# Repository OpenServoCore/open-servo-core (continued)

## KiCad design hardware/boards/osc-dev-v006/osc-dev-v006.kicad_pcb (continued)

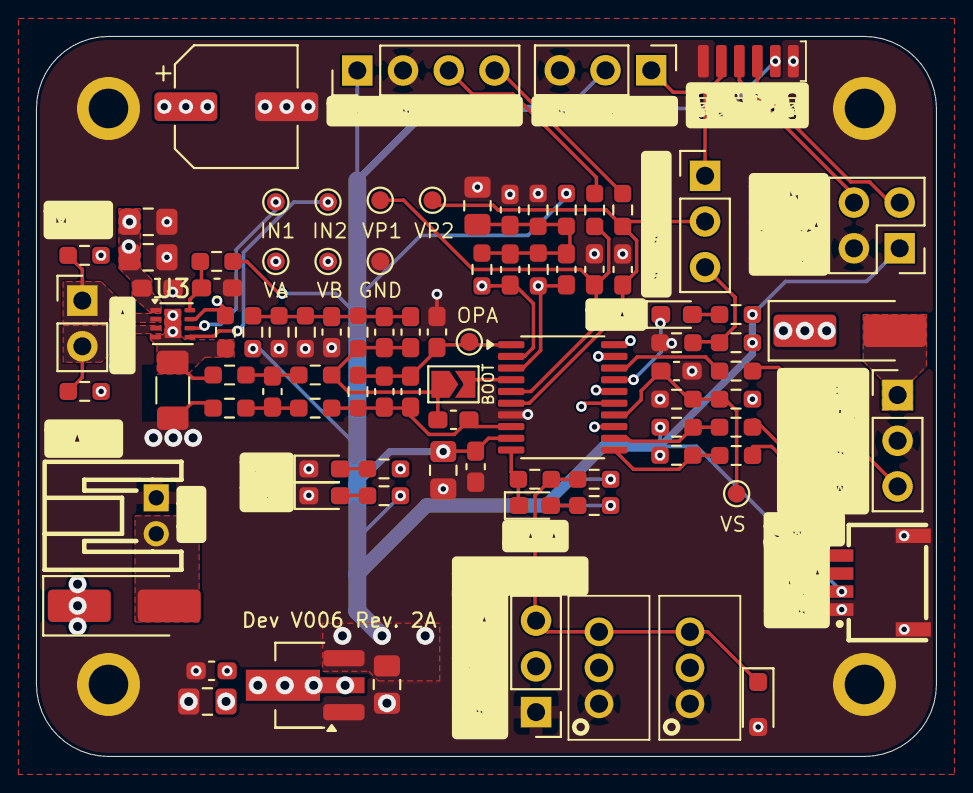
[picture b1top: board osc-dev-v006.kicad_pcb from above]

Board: 6 copper layers, 50.0 x 40.0 mm, 99 parts (0 on the bottom side), 46 nets.

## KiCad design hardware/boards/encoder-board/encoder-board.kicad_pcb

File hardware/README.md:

# KiCad Component Management

## Component Linkage System

### Directory Structure

```
hardware/
├── shared.kicad_sym        # Symbol library
├── shared.pretty/           # Footprint library
├── shared.3dshapes/         # 3D models
├── templates/jlc4l_1v6mm/   # Template project (canonical reference)
└── boards/*/                # Board projects
```

### Linkage Patterns

#### 1. Project → Libraries

Projects link to shared libraries via `sym-lib-table` and `fp-lib-table`:

- Symbol library: `${KIPRJMOD}/../../shared.kicad_sym`
- Footprint library: `${KIPRJMOD}/../../shared.pretty`

#### 2. Symbol → Footprint

Symbols in `shared.kicad_sym` reference footprints using library prefix:

- Format: `"shared:FOOTPRINT_NAME"`
- Example: `"shared:UQFN-20_L3.0-W3.0-P0.40-BL-EP1.7"`

#### 3. Footprint → 3D Model

Footprints in `shared.pretty/` reference 3D models using relative paths:

- Format: `${KIPRJMOD}/../../shared.3dshapes/MODEL_NAME.wrl`
- Example: `${KIPRJMOD}/../../shared.3dshapes/UQFN-20_L3.0-W3.0-P0.40-BL-EP1.7.wrl`

## Component Acquisition Strategy

1. Navigate to a board or template directory:

   ```bash
   cd hardware/templates/jlc4l_1v6mm
   ```

2. Download component:

   ```bash
   easyeda2kicad --full --lcsc_id <LCSC_ID> --output ../../shared --overwrite --project-relative
   ```

3. Fix 3D model paths in footprint files:
   - Find: `${KIPRJMOD}././shared.3dshapes`
   - Replace: `${KIPRJMOD}/../../shared.3dshapes`

4. In `shared.kicad_sym`, rename the `LCSC Part` property to `LCSC` on the downloaded symbol.

## Post-Import Checklist

- [ ] Symbol has correct footprint reference (`"shared:FOOTPRINT_NAME"`)
- [ ] Footprint has correct 3D model path (`${KIPRJMOD}/../../shared.3dshapes/...`)
- [ ] Pin types are correctly set: power_in (VCC/GND), input (control/data in), output (data out), passive (connectors) - NO "unspecified" pins allowed
- [ ] 3D model displays correctly in KiCad 3D viewer
- [ ] Symbol uses `LCSC` property (not `LCSC Part`) for the part number
- [ ] Component source documented (LCSC part number)

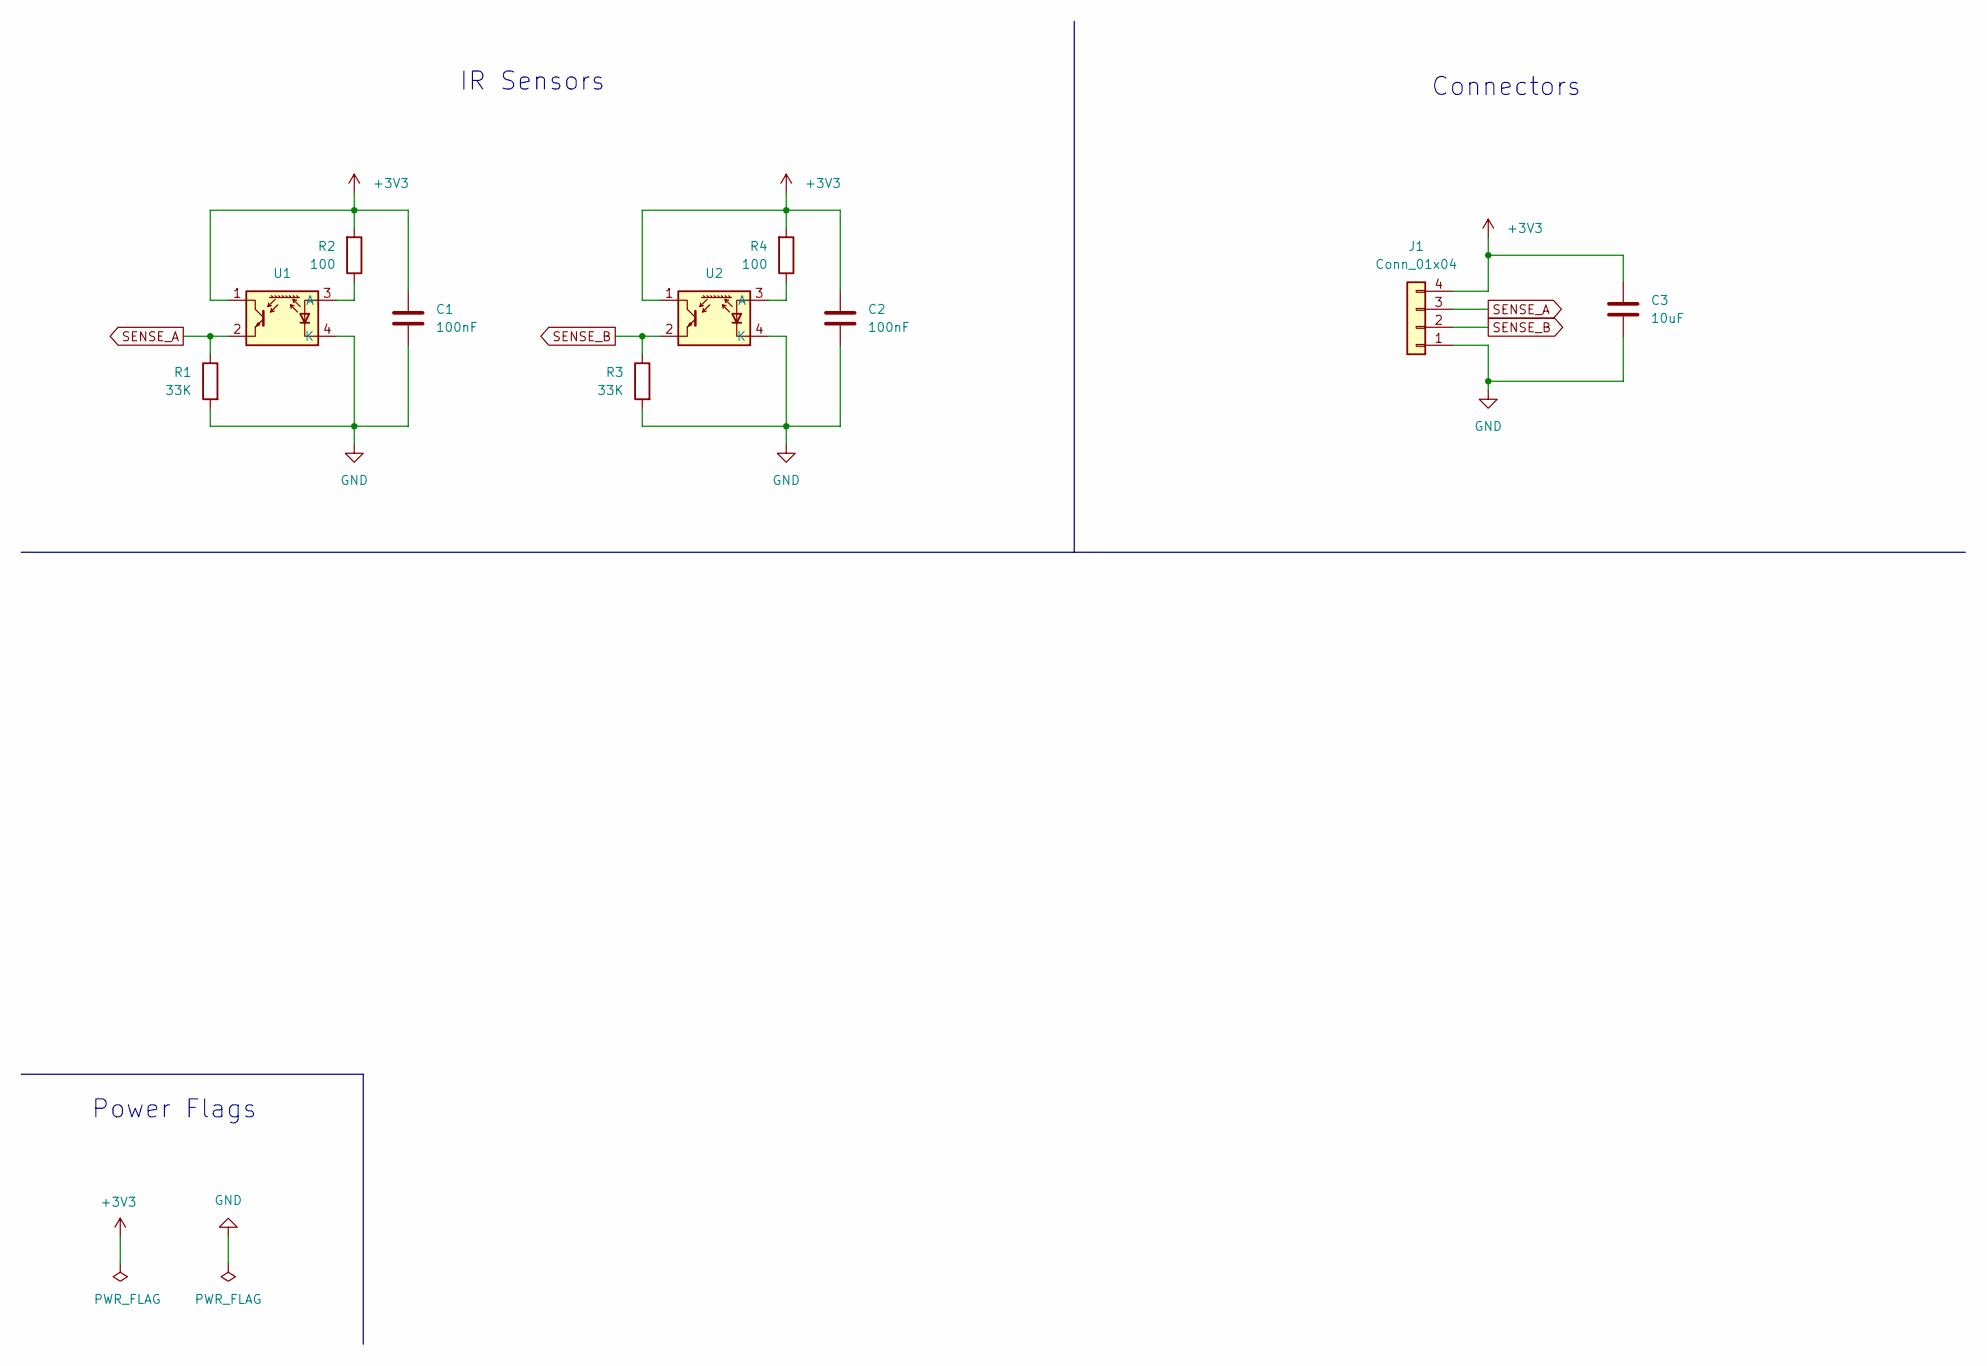
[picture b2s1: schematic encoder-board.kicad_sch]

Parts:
C1, C2: 100nF; C_0805_2012Metric_Pad1.18x1.45mm_HandSolder; LCSC C49678
C3: 10uF; C_0805_2012Metric_Pad1.18x1.45mm_HandSolder; LCSC C15850
J1: Conn_01x04; PinHeader_1x04_P2.54mm_Vertical; LCSC C780062
R1, R3: 33K; R_0805_2012Metric_Pad1.20x1.40mm_HandSolder; LCSC C17633
R2, R4: 100; R_0805_2012Metric_Pad1.20x1.40mm_HandSolder; LCSC C17408
U1, U2: ITR1204SR10A_TR(BY); OPTO-SMD-4_ITR1204SR10A; LCSC C475373

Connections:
+3V3: C1.1, C2.1, C3.1, J1.4, R2.2, R4.2, U1.1, U2.1
GND: C1.2, C2.2, C3.2, J1.1, R1.2, R3.2, U1.4 (K), U2.4 (K)
unnamed: R2.1, U1.3 (A)
unnamed: R4.1, U2.3 (A)
SENSE_A: J1.3, R1.1, U1.2
SENSE_B: J1.2, R3.1, U2.2

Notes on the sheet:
IR Sensors
Connectors
Power Flags

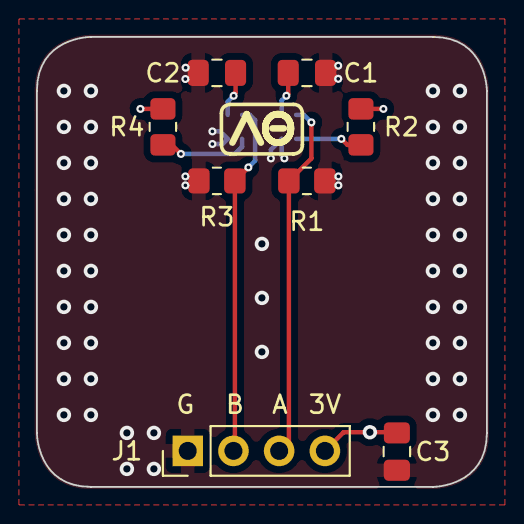
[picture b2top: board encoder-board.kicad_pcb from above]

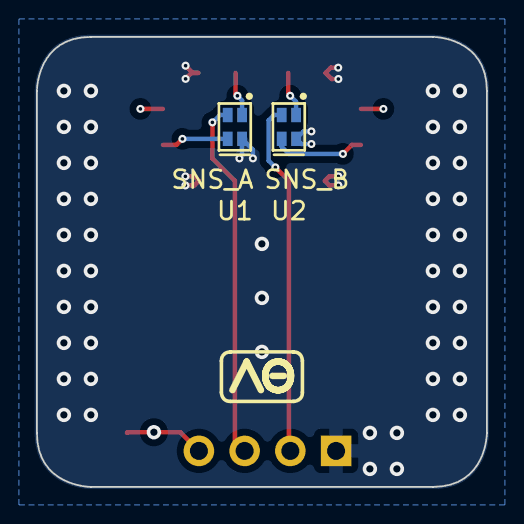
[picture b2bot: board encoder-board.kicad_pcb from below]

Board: 4 copper layers, 25.0 x 25.0 mm, 10 parts (2 on the bottom side), 6 nets.

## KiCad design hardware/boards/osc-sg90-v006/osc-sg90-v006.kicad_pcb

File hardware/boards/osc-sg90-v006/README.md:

# OSC SG90 CH32

> ⚠️ **Designed, not spun. Pre-fabrication, pre-bringup.**
> This board has never been fabbed. Numbers and behaviour described below are **design intent**, not measured. The schematic and layout exist; firmware v2 now runs on the dev board (the bus transport is silicon-proven) but has never run on *this* board. Don't fab this without doing your own review first, and expect changes when bringup finally happens.

OpenServoCore swap board for SG90-class hobby servos. Compact, double-sided, designed to physically replace the factory PCB inside an SG90 case. CH32V006-based, single-wire TTL servo bus (osc-native protocol), drop-in mechanical fit.

## Overview

- **MCU** — CH32V006F8U6 (RISC-V, 48 MHz, 62 KB flash, 8 KB RAM).
- **Motor driver** — TI DRV8837 H-bridge (1.8 A peak, IN1/IN2 PWM).
- **LDO** — TPAP2210K-3.3, 3.3 V logic rail.
- **UART buffer** — SN74LVC1G07 open-drain for the half-duplex TTL bus.
- **Current shunt** — 25 mΩ, 1 % on the low side.
- **Power input** — 3.3-8.4 V (1S-2S LiPo) via the servo cable.
- **Debug** — 4-pad SWD interface for WCH-LinkE.
- **Position feedback** — existing servo potentiometer wiper.
- **Form factor** — 10 × 12.5 mm, double-sided assembly.

## Connectors

### Servo cable — J1 (1×3, through-hole pads)

Standard hobby-servo 3-wire pinout, but the signal pin carries half-duplex UART instead of PWM:

| Pin | Net    | Notes                                   |
| --- | ------ | --------------------------------------- |
| 1   | `VIN`  | 3.3-8.4 V (1S-2S LiPo).                 |
| 2   | `DATA` | Half-duplex UART, baud TBD by firmware. |
| 3   | `GND`  |                                         |

### Motor — J2 (2 wire pads)

Solder directly to the SG90 motor leads.

| Pad    | Net              |
| ------ | ---------------- |
| `OUTA` | Motor terminal A |
| `OUTB` | Motor terminal B |

### Potentiometer — J3 (3 pads)

Connects to the existing servo potentiometer.

| Pad    | Net          |
| ------ | ------------ |
| `+3V3` | Pot top rail |
| `VPOS` | Wiper        |
| `GND`  | Pot ground   |

### Debug — J4 (4 pads, 1.27 mm pitch)

Single-wire SWD for WCH-LinkE. Programmed via `wlink` / `probe-rs`. Firmware build instructions land when firmware v2 starts; until then there's nothing to flash.

| Pad | Net     |
| --- | ------- |
| 1   | `+3V3`  |
| 2   | `GND`   |
| 3   | `SWDIO` |
| 4   | `NC`    |

## Design intent

These are the targets the board was laid out around. None are measured.

- **Power architecture** — VIN routes to the DRV8837 directly; 3.3 V logic rail off the TPAP2210K LDO. Bulk capacitance is 2× 10 µF on VIN. PGND/GND joined at a single net tie.
- **Position sensing** — 12-bit ADC on `VPOS` with an RC filter (10 kΩ + 100 nF, fc ≈ 160 Hz) to suppress wiper noise. Sub-degree resolution is the design goal; actual precision waits on bringup and firmware oversampling.
- **Voltage sensing** — 20 kΩ / 10 kΩ dividers (ratio 0.333) on `VINS`, `VSNA`, `VSNB`. 8.4 V → 2.8 V at the ADC.
- **Current sensing** — 25 mΩ low-side shunt, sized for the DRV8837's ~1.76 A peak via `R_shunt ≈ 44 mV / I_stall`, so the hardware stall-detect path trips near the driver's max output. Raw V_shunt = 25 mV at 1 A; firmware sets ADC sampling, gain path, and software overcurrent threshold.
- **Communication** — single-wire half-duplex TTL servo bus (Dynamixel-TTL electrical layer; the wire protocol is [osc-native](../../../docs/osc-native-protocol.md)). The SN74LVC1G07 open-drain buffer enables bidirectional comms over the single `DATA` line. Bus rates: 0.5-3 Mbaud, default 1 M.
- **Protection** — PESD5V0L1UL TVS on `DATA`.

## Assembly

Double-sided assembly, no vias-in-pads. Suitable for hot-plate / hot-air / IR reflow, or JLCPCB SMT. The board is 8-layer for routing density at this size.

## Mechanical fit

Designed to drop into a standard SG90 servo case:

- Motor leads solder to `OUTA` / `OUTB`.
- Pot wiper connects to `J3`.
- Servo cable connects to `J1`.
- Debug pads remain accessible through the case opening for bringup / reflashing.

Pad spacing for motor leads and debug pitch are still **to be confirmed against a physical case** when first boards arrive.

## License

Hardware files (schematic, layout, board files in this directory) are licensed under [CERN-OHL-P v2.0](../../../LICENSE-HARDWARE). See the [top-level README](../../../README.md#license) for the full licensing picture.

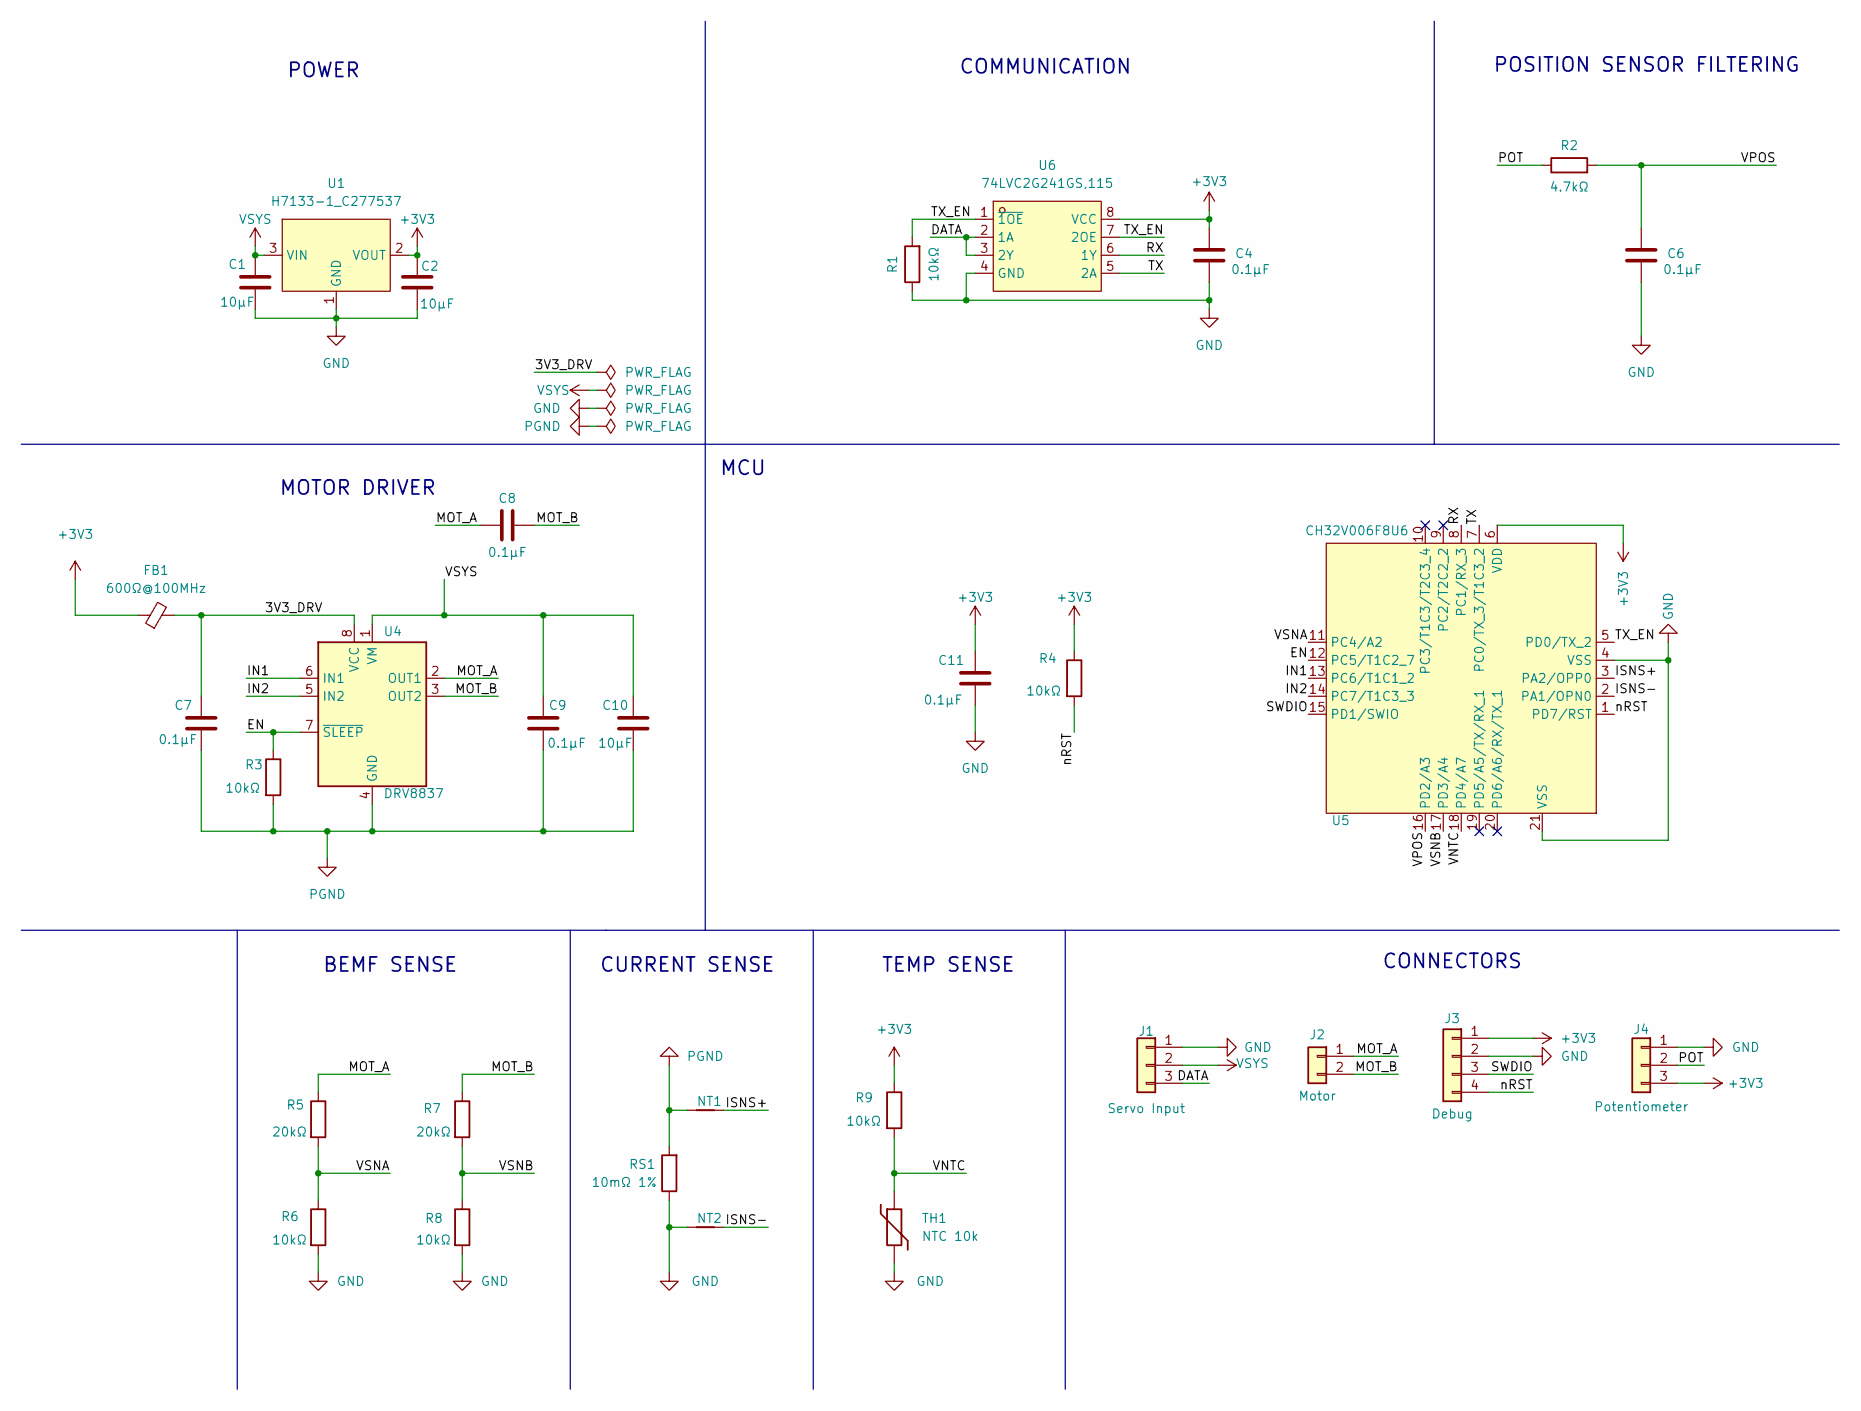
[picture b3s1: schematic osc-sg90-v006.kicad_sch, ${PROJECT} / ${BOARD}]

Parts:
C1, C2, C10: 10µF; C_0603_1608Metric; LCSC C96446
C4, C6, C7, C8, C9, C11: 0.1µF; C_0402_1005Metric; LCSC C1525
FB1: 600Ω@100MHz; L_0402_1005Metric; LCSC C76884
J1: Servo Input; Servo_Output_Pads
J2: Motor; Motor_Wire_Pads
J3: Debug; Debug_Pads_1x4_P1.27mm
J4: Potentiometer; Pot_Wire_Pads
NT1, NT2: NetTie_2; NetTie-2_SMD_0.127mm
R1, R3, R4, R6, R8, R9: 10kΩ; R_0402_1005Metric; LCSC C25744
R2: 4.7kΩ; R_0402_1005Metric; LCSC C25900
R5, R7: 20kΩ; R_0402_1005Metric; LCSC C25765
RS1: 10mΩ 1%; R_0805_2012Metric; LCSC C163089
TH1: NTC 10k; R_0402_1005Metric; LCSC C77131
U1: H7133-1_C277537; SOT-23-3_L2.9-W1.3-P1.90-LS2.4-BR; LCSC Part C277537
U4: DRV8837; WSON-8-1EP_2x2mm_P0.5mm_EP0.9x1.6mm; LCSC C39159
U5: CH32V006F8U6; UQFN-20_L3.0-W3.0-P0.40-BL-EP1.7; LCSC C42431288
U6: 74LVC2G241GS,115; XSON-8_L1.4-W1.0-P0.35-S0.55-BL; LCSC C548628

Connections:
+3V3: C2.1, C4.1, C11.1, FB1.1, J3.1, J4.3, R4.1, R9.1, U1.2 (VOUT), U5.6 (VDD), U6.8 (VCC)
/3V3_DRV: C7.1, FB1.2, U4.8 (VCC)
/DATA: J1.3, U6.2 (1A), U6.3 (2Y)
/EN: R3.1, U4.7 (~SLEEP), U5.12 (PC5/T1C2_7)
/IN1: U4.6 (IN1), U5.13 (PC6/T1C1_2)
/IN2: U4.5 (IN2), U5.14 (PC7/T1C3_3)
/ISNS+: NT1.1, U5.3 (PA2/OPP0)
/ISNS-: NT2.1, U5.2 (PA1/OPN0)
/MOT_A: C8.1, J2.1, R5.1, U4.2 (OUT1)
/MOT_B: C8.2, J2.2, R7.1, U4.3 (OUT2)
/POT: J4.2, R2.1
/RX: U5.8 (PC1/RX_3), U6.6 (1Y)
/SWDIO: J3.3, U5.15 (PD1/SWIO)
/TX: U5.7 (PC0/TX_3/T1C3_2), U6.5 (2A)
/TX_EN: R1.2, U5.5 (PD0/TX_2), U6.1 (~1OE), U6.7 (2OE)
/VNTC: R9.2, TH1.1, U5.18 (PD4/A7)
/VPOS: C6.1, R2.2, U5.16 (PD2/A3)
/VSNA: R5.2, R6.1, U5.11 (PC4/A2)
/VSNB: R7.2, R8.1, U5.17 (PD3/A4)
/nRST: J3.4, R4.2, U5.1 (PD7/RST)
GND: C1.2, C2.2, C4.2, C6.2, C11.2, J1.1, J3.2, J4.1, NT2.2, R1.1, R6.2, R8.2, RS1.1, TH1.2, U1.1 (GND), U5.4 (VSS), U5.21 (VSS), U6.4 (GND)
PGND: C7.2, C9.2, C10.2, NT1.2, R3.2, RS1.2, U4.4 (GND), U4.9 (GND)
VSYS: C1.1, C9.1, C10.1, J1.2, U1.3 (VIN), U4.1 (VM)

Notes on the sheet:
POWER
MOTOR DRIVER
BEMF SENSE
CONNECTORS
TEMP SENSE
CURRENT SENSE
COMMUNICATION
MCU
POSITION SENSOR FILTERING

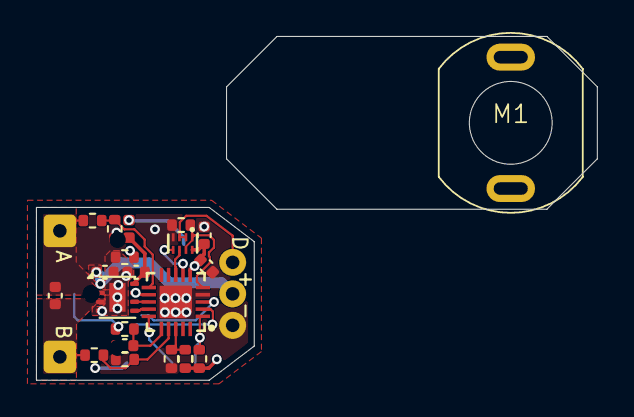
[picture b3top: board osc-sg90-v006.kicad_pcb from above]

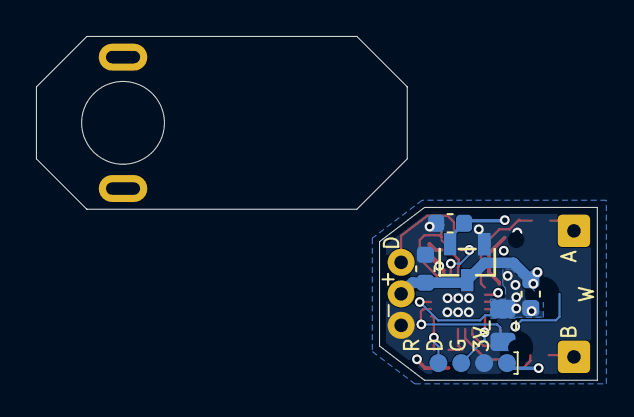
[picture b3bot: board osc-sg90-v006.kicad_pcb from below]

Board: 4 copper layers, 31.2 x 19.1 mm, 33 parts (8 on the bottom side), 23 nets.

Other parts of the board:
J4#2: Potentiometer; Pot_Wire_Pads
M1: SG90_Motor

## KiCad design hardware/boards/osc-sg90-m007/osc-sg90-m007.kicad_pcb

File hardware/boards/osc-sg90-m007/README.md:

# OSC SG90 M007

> ⚠️ **Designed, not spun. Pre-fabrication, pre-bringup.**
> This board has never been fabbed. Numbers and behaviour described below are **design intent**, not measured. The M007 layout is fully routed and DRC-clean, but it exists as a feasibility study - the dev board gets built and validated first. Don't fab this without doing your own review.

OpenServoCore swap board for SG90-class hobby servos. Compact, double-sided, designed to physically replace the factory PCB inside an SG90 case. CH32M007-based: one IC carries the MCU, the 3-phase gate pre-driver, the HV regulator, and the current-sense amplifier - no motor-driver IC, no LDO, no bus buffer.

## Overview

- **MCU + driver** - CH32M007E8U7 (QFN-26, 3×3 mm): 48 MHz RISC-V, integrated gate pre-driver with hardware dead-time, internal HV regulator (VSYS → 5 V VDD), on-die OPA/PGA current sense, CMP overcurrent → TIM1 brake in silicon.
- **Bridge** - 2× MCC MCMNP2065A (dual complementary N+P, DFN2020-6L 2×2 mm; N 20 mΩ / P 44 mΩ @4.5 V), one package per half-bridge, gates driven directly from HO/LO (no gate resistors), 100 kΩ gate keepers. Gates are ±10 V rated: legal because gate drive is rail-limited below the driver's 9.5 V clamp floor - see the 2S pin below.
- **Current shunts** - 2× 75 mΩ 1 % 0.5 W 0805 (Yageo PE series), per-leg low-side, Kelvin taps via net-ties into the on-die PGA (G = 16 differential).
- **Power input** - 6.5-9 V, **2S only** - the bridge's ±10 V gate rating pins this board to 2S (the dev board's 6.5-15 V window needs the ±20 V SOT-23-6 part). Firmware must interlock PWM above ~9 V rail (VSYS reads through the phase dividers). The gate-driver UVLO sets the 6.5 V floor; 1S and USB-5V cannot drive the bridge. VHREG is strapped to VHV (no series resistor).
- **Bus** - single-wire half-duplex UART (osc-native protocol), direct USART HDSEL on PB3 - no buffer. 33 Ω series + PESD5V0L1BA on DATA. 0.5-3 Mbaud.
- **Temperature** - on-board 10 kΩ NTC, B25/50 = 3380 K (NCP15XH103, 0402). Note: the dev board's NTC is 3950 K - the B constant is board-seeded config, not shared firmware math.
- **Position feedback** - existing servo potentiometer wiper, 4.7 kΩ + 100 nF at the ADC pin.
- **Passives** - smallest-package policy: 10 µF and 2.2 µF are 0603, all other R/C are 0402, shunts are the 1206 exception. JLC-basic parts wherever one exists; every part carries `LCSC`, `MFPN`, `Datasheet`, and `JLC_Basic` fields.
- **Form factor** - 10 × 12.5 mm target, double-sided assembly.

## Connectors

### Servo cable - J1 (1×3, wire pads)

Standard hobby-servo 3-wire cable; the signal wire carries the osc-native bus instead of PWM.

Center-power, same order as the dev board's bus connectors - an offset misplug never puts VSYS on DATA.

| Pad | Net    | Notes                       |
| --- | ------ | --------------------------- |
| 1   | `DATA` | Half-duplex osc-native bus. |
| 2   | `VSYS` | 6.5-15 V (2S/3S).           |
| 3   | `GND`  |                             |

### Motor - J2 (2 wire pads)

Solder directly to the SG90 motor leads (phase A / phase B of the bridge).

### Potentiometer - J4 (3 pads)

| Pad   | Net   | Notes              |
| ----- | ----- | ------------------ |
| `+5V` | `+5V` | Pot top rail.      |
| `POT` | `POT` | Wiper, via 4.7 kΩ. |
| `GND` | `GND` | Pot ground.        |

### Debug - J3 (4 pads, 1.0 mm pitch)

Single-wire SWIO for WCH-LinkE (`wlink`).

| Pad | Net    |
| --- | ------ |
| 1   | `+5V`  |
| 2   | `GND`  |
| 3   | `SWIO` |
| 4   | `nRST` |

## Design intent

These are the targets the schematic was drawn around. None are measured.

- **Decoupling** - DS Fig 3-1-3 floor exactly: 10 µF + 0.1 µF (25 V) on VHV, 2.2 µF on VHREG, 10 µF + 0.1 µF on VDD. No bulk beyond that - the single VHV 10 µF (bias-derated ~5 µF at 8.4 V) is the entire on-servo reservoir. This assumes the hub/BEC end of the harness carries the real per-branch bulk; hot-plug onto a charged pack rings a ceramic-only input and is a first-article scope item.
- **Voltage sensing** - 20 kΩ / 10 kΩ dividers on both phases (VSNA/VSNB); 15 V → 5 V at the ADC. Rail voltage reads through the phase dividers with the bridge parked high.
- **Current sensing** - per-leg shunts into the on-die PGA; CMP2 trip window ~2.5-2.75 A between worst 2S stall and harm (range budget in the bringup repo's `osc-dev-m007-pinout.md`).
- **Protection** - PESD5V0X1BCSFYL on DATA (ultra-low-capacitance, DFN1006-2); hardware OCP internal to the M007; no reverse-polarity protection (captive harness).

## Assembly

Double-sided assembly, 0402-and-up, suitable for JLCPCB economic SMT (all jellybeans are basic parts; extended types: MCU, FETs, shunts, PESD, 2.2 µF, 25 V 0402 100 nF, NTC). Motor, pot, and servo-cable connections are hand-soldered wire pads during the servo transplant.

## Mechanical fit

Designed to drop into a standard SG90 servo case. Pad spacing for motor leads and debug pitch are still **to be confirmed against a physical case** when first boards arrive.

## License

Hardware files (schematic, layout, board files in this directory) are licensed under [CERN-OHL-P v2.0](../../../LICENSE-HARDWARE). See the [top-level README](../../../README.md#license) for the full licensing picture.

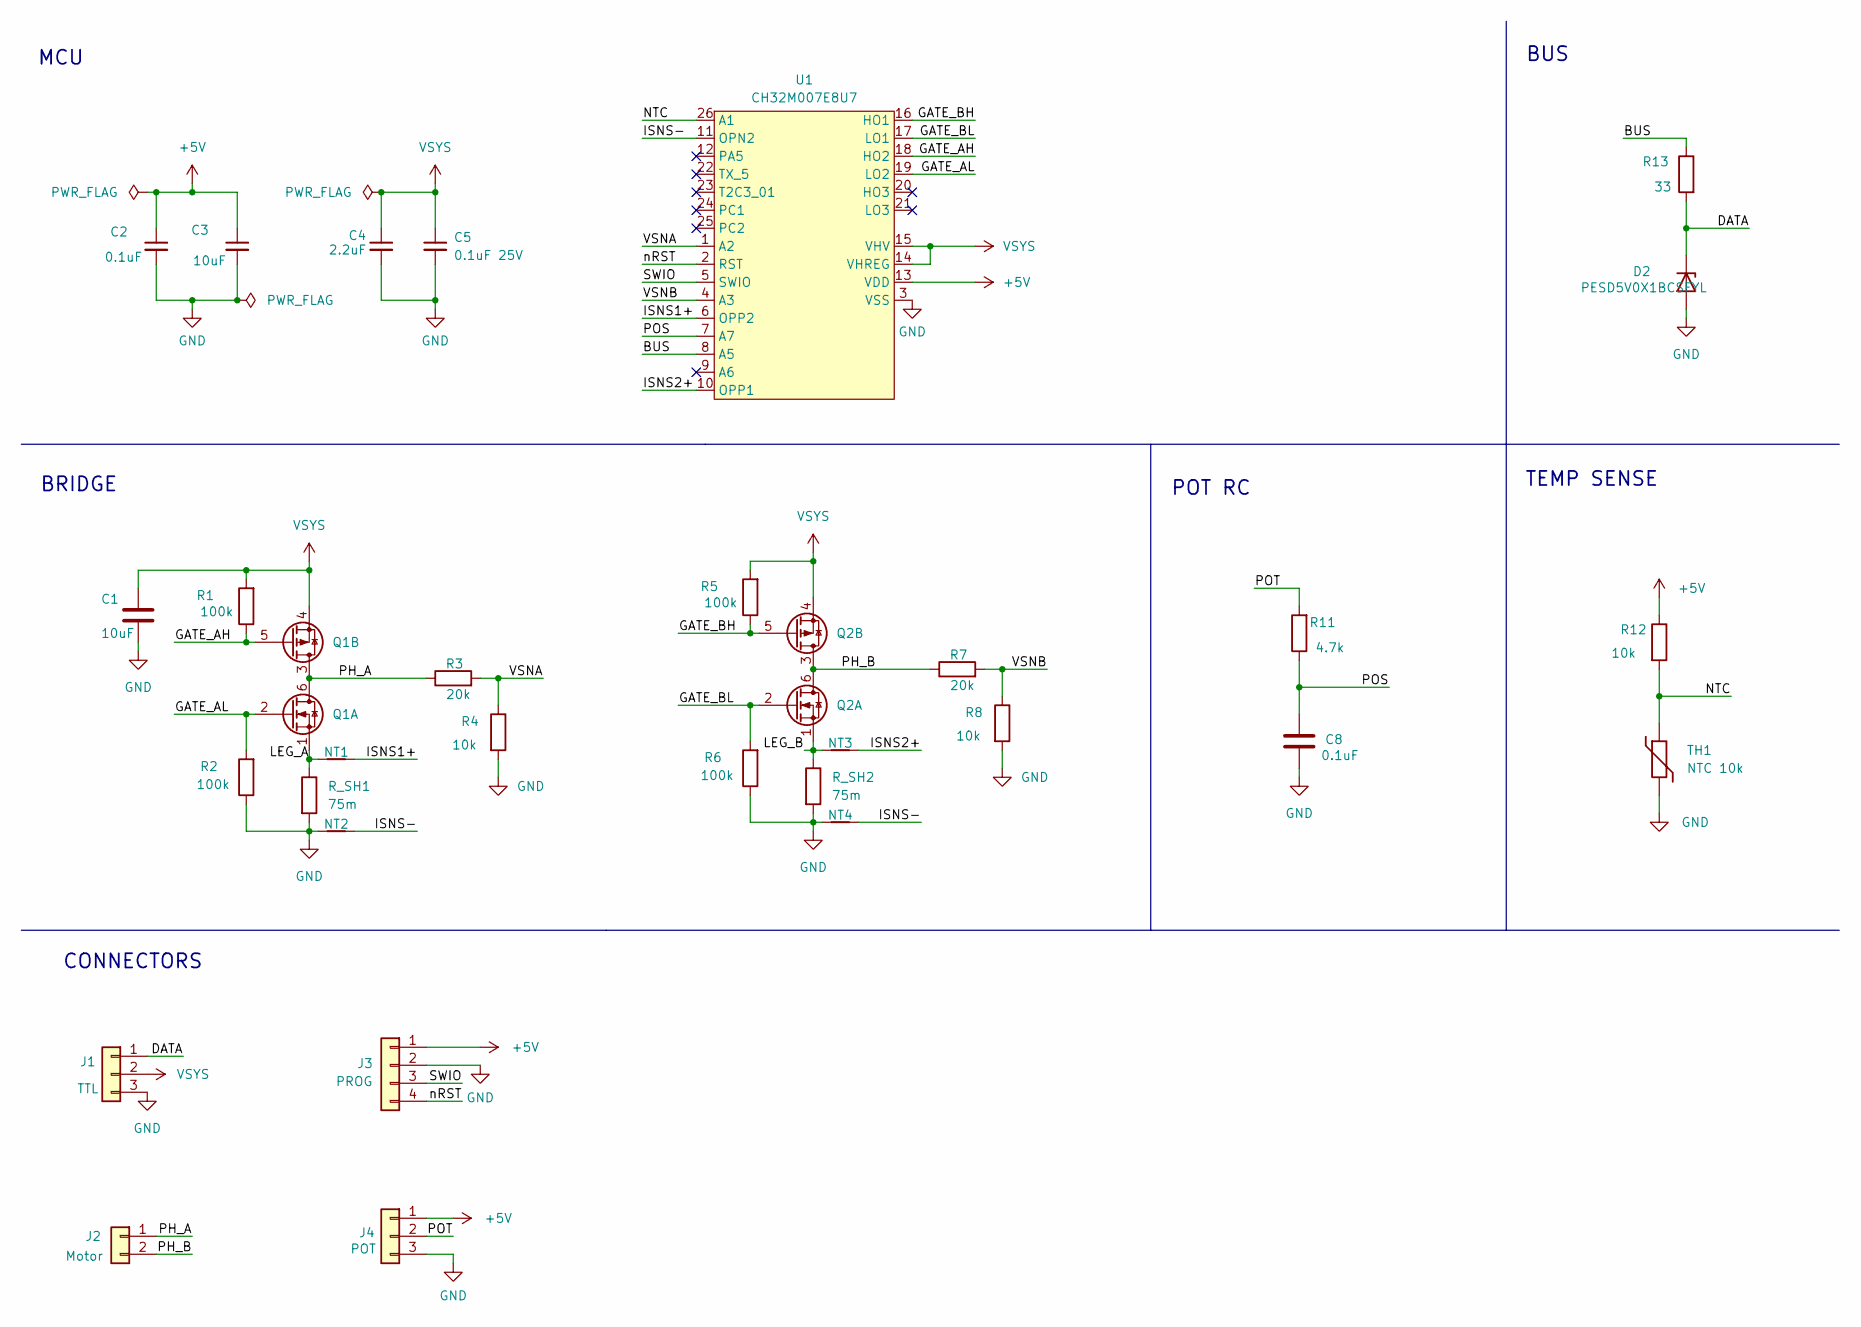
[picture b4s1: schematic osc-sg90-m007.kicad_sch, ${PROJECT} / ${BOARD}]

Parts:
C1, C3: 10uF; C_0603_1608Metric; JLC_Basic yes
C2: 0.1uF; C_0402_1005Metric; JLC_Basic yes
C4: 2.2uF; C_0603_1608Metric; JLC_Basic no
C5: 0.1uF 25V; C_0402_1005Metric; JLC_Basic no
C8: 0.1uF; C_0402_1005Metric; LCSC C1525
D2: PESD5V0X1BCSFYL; D_SOD-882; LCSC C2443412
J1: TTL; Servo_Output_Pads
J2: Motor; Motor_Wire_Pads
J3: PROG; Debug_Pads_1x4_P1.0mm
J4: POT; Pot_Wire_Pads
NT1, NT2, NT3, NT4: NetTie_2; NetTie-2_SMD_0.127mm
Q1, Q2: MCMNP2065A-TP; DFN2020-6L; JLC_Basic no
R1, R2, R5, R6: 100k; R_0402_1005Metric; JLC_Basic yes
R3, R7: 20k; R_0402_1005Metric; LCSC C25765
R4, R8, R12: 10k; R_0402_1005Metric; LCSC C25744
R11: 4.7k; R_0402_1005Metric; LCSC C25900
R13: 33; R_0402_1005Metric; LCSC C25105
R_SH1, R_SH2: 75m; R_0603_1608Metric; JLC_Basic no
TH1: NTC 10k; R_0402_1005Metric; LCSC C77131
U1: CH32M007E8U7; QFN-26_3x3mm_P0.4mm; JLC_Basic no

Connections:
+5V: C2.1, C3.1, J3.1, J4.1, R12.1, U1.13 (VDD)
/BUS: R13.1, U1.8 (A5)
/DATA: D2.1 (K), J1.1, R13.2
/GATE_AH: Q1.5 (G), R1.1, U1.18 (HO2)
/GATE_AL: Q1.2 (G), R2.2, U1.19 (LO2)
/GATE_BH: Q2.5 (G), R5.1, U1.16 (HO1)
/GATE_BL: Q2.2 (G), R6.2, U1.17 (LO1)
/ISNS1+: NT1.2, U1.6 (OPP2)
/ISNS2+: NT3.2, U1.10 (OPP1)
/ISNS-: NT2.2, NT4.2, U1.11 (OPN2)
/LEG_A: NT1.1, Q1.1 (S), R_SH1.1
/LEG_B: NT3.1, Q2.1 (S), R_SH2.1
/NTC: R12.2, TH1.1, U1.26 (A1)
/PH_A: J2.1, Q1.3 (D), Q1.6 (D), R3.1
/PH_B: J2.2, Q2.3 (D), Q2.6 (D), R7.1
/POS: C8.1, R11.1, U1.7 (A7)
/POT: J4.2, R11.2
/SWIO: J3.3, U1.5 (SWIO)
/VSNA: R3.2, R4.1, U1.1 (A2)
/VSNB: R7.2, R8.1, U1.4 (A3)
/nRST: J3.4, U1.2 (RST)
GND: C1.2, C2.2, C3.2, C4.2, C5.2, C8.2, D2.2 (A), J1.3, J3.2, J4.3, NT2.1, NT4.1, R2.1, R4.2, R6.1, R8.2, R_SH1.2, R_SH2.2, TH1.2, U1.3 (VSS)
VSYS: C1.1, C4.1, C5.1, J1.2, Q1.4 (S), Q2.4 (S), R1.2, R5.2, U1.14 (VHREG), U1.15 (VHV)

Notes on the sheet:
CONNECTORS
TEMP SENSE
BUS
MCU
POT RC
BRIDGE

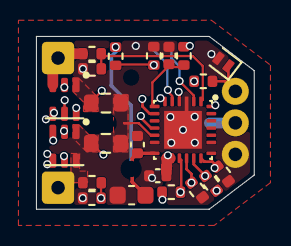
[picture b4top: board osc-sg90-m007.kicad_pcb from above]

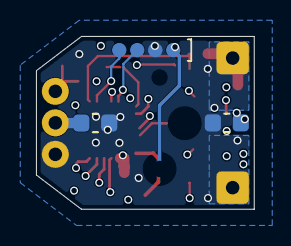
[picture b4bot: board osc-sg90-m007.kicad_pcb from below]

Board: 6 copper layers, 12.1 x 9.6 mm, 32 parts (3 on the bottom side), 23 nets.

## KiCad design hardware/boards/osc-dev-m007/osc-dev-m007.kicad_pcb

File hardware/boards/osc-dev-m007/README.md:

# OSC Dev M007 - Rev A

> ⚠️ **Designed, not fabricated yet.**
> No physical copy of this board has been built or tested. Everything below is design intent, written before the first article. If you fab one before that happens, you are the test pilot.

The development board for OpenServoCore's M007 servo brain. One chip - the CH32M007, 3 × 3 mm - contains the microcontroller, the motor gate driver, the current-sense amplifier, and the 5 V regulator. Add six small MOSFETs and it drives a brushed servo motor (SG90/MG90 class) or a small 3-phase BLDC, measures motor current, reads a position sensor, and talks on a single-wire bus.

This is the bench version: everything on a labelled connector or test point, screw terminals for the motor, room to probe. The matching production board ([osc-sg90-m007](../osc-sg90-m007/)) squeezes the same circuit into an SG90 case; this one spreads it out on 50 × 50 mm so it is easy to work on.

## What you need

- **Power between 6.5 and 15 V** - a 2S or 3S LiPo, or a bench supply.
- A **WCH-LinkE** debug probe (about $4) to flash firmware and read logs.
- Something to move: a gutted hobby servo (motor + potentiometer), a bare DC motor, or a small gimbal-class BLDC.

## Board tour

Every connector is labelled on the silkscreen:

| Silk label | What it is |
| --- | --- |
| `+` `-` (JST, top left) | Battery input, 6.5-15 V, reverse-polarity protected |
| `A B C` (screw terminal) | Motor. Brushed motor uses A and B; BLDC uses all three |
| `DATA VS GND` (two JSTs) | The servo bus. Two jacks so boards daisy-chain; `VS` is the raw supply rail |
| `POT 5V GND` | Servo potentiometer (wiper to `POT`) |
| `ENC 5V GND` | Encoder input - analog voltage, or PWM like an AS5600 |
| `INT NTC EXT` | Temperature source jumper: onboard sensor (`INT`) or your own thermistor on the `NTC GND` header (`EXT`) |
| `SWDIO G 5V G RST` | Debug/flash header for the WCH-LinkE |
| `G VRG G VS G 5V` | Power-rail probe header, every second pin is ground |
| `NTC POS ENC LED GND DATA` | Signal breakout for a scope or logic analyzer |
| `DB0` `DB1` `DB2` + `GND` | Firmware timing probe pads |
| `RGB` | WS2812 status LED |
| `VS` / `5V` LEDs | Power indicators: motor rail / logic rail |
| `RESET` | Reset button |

## Powering it

Three ways in, and they can be combined freely:

1. **Battery jack** - 2S or 3S LiPo. This input has a protection diode, so a reversed pack does nothing instead of damage. The diode costs ~0.4 V, so a nearly-empty 2S may dip under the motor's 6.5 V floor a little early.
2. **Bus jack `VS` pin** - wired straight to the rail, no diode. This is how a servo receives power in a robot, and the better path for high-current bench work.
3. **The LinkE's 5 V** through the debug header - powers the logic only.

The one rule to internalize: **the motor only runs above about 6.5 V.** The gate driver refuses to switch below that - a built-in safety property, not a fault. In practice:

- On 5 V from the LinkE, everything except the motor works: the MCU boots, firmware flashes, the bus talks, sensors read. **A dark motor on USB-level power is normal, not a broken board.**
- A 1S battery (4.2 V) can never drive the motor. 2S minimum.

The FETs are sized for roughly 2 A continuous and 3 A bursts - enough for every SG90/MG90/MG996R-class servo. A hardware comparator cuts the bridge at about 2.5-2.75 A on its own, even if firmware hangs.

## Hooking up a servo

The core experiment - turning a $2 servo into a smart one:

1. Open the servo and unsolder its factory PCB.
2. Motor wires → screw terminals `A` and `B`.
3. Potentiometer → the `POT 5V GND` header, wiper to `POT`.
4. Power and bus → one of the JST bus jacks.

The board measures motor current through two small shunt resistors and the chip's built-in amplifier - about 1 mA per ADC count - so firmware can feel load and stall without any extra parts.

For temperature, the onboard sensor (`INT` jumper) tracks the board. For motor experiments, tape a 10 k NTC thermistor to the motor can, wire it to `NTC GND`, and move the jumper to `EXT`.

## Talking to it

The bus is one shared 5 V wire plus power and ground. Every servo hangs on the same three wires, each with its own address, at up to 3 Mbaud. The wire format is the [osc-native protocol](../../../docs/osc-native-protocol.md) - OSC's own break-framed protocol, in the spirit of Dynamixel but designed for very cheap MCUs.

On the host side, a second WCH-LinkE flashed with the [adapter firmware](../../../firmware/boards/osc-adapter-wchlinke/) becomes the USB-to-bus interface.

## Flashing firmware

Connect a WCH-LinkE to the debug header - `SWDIO` and `G` at minimum, plus `5V` if the probe should power the board - and flash with [wlink](https://github.com/ch32-rs/wlink). Firmware v2 for the M007 is in bring-up; the transport and protocol layers are proven on the V006 family and the M007 uses the same USART hardware. Check the repo root [README](../../../README.md) for current status.

## Specs

| | |
| --- | --- |
| Brain | CH32M007E8U7 - 48 MHz RISC-V MCU + gate driver + current-sense amp + 5 V regulator, one QFN-26 |
| Supply | 6.5-15 V (2S/3S LiPo) |
| Motor | Brushed H-bridge or 3-phase BLDC, ~2 A continuous / 3 A burst |
| Current sense | Two 75 mΩ shunts, on-die amplifier, ~1 mA resolution |
| Overcurrent | Hardware comparator trip at ~2.5-2.75 A |
| Feedback | Potentiometer, analog/PWM encoder, NTC (onboard or external) |
| Bus | Single-wire half-duplex, 5 V logic, 0.5-3 Mbaud |
| Size | 50 × 50 mm, 6-layer, M2 mounting holes |

## Building one

The board is designed around JLCPCB's 6-layer promo: 50 × 50 mm, all vias 0.3 mm, epoxy-filled vias (select "Epoxy Filled & Capped"), which prices at a few dollars for five boards and forces ENIG (gold) finish - which also makes hand assembly nicer.

- Every part has its LCSC number in the schematic; the passives are 0805, chosen for easy hand soldering.
- One genuinely hard joint: the QFN-26 with its center pad. That pad ties into the board's internal copper planes, which soak up heat - hot air from the top alone usually can't get the joint to reflow. Heat the board from below with a hotplate (paste stencil, place the chip, reflow the whole side), using hot air on top only as a finisher. Everything else is beginner-friendly.
- Parts marked DNP ("do not populate") in the schematic are options and tuning pads. Leave them empty - that IS the standard build. Some of them change how the board behaves (shunt value, sense filtering), so only mount one if you know exactly why you want it.

## More reading

- [osc-native protocol](../../../docs/osc-native-protocol.md) - the wire protocol
- [servo transport](../../../docs/osc-servo-transport.md) - how the servo side keeps up at 3 Mbaud
- [design history](../../../docs/design-history.md) - how the project got here

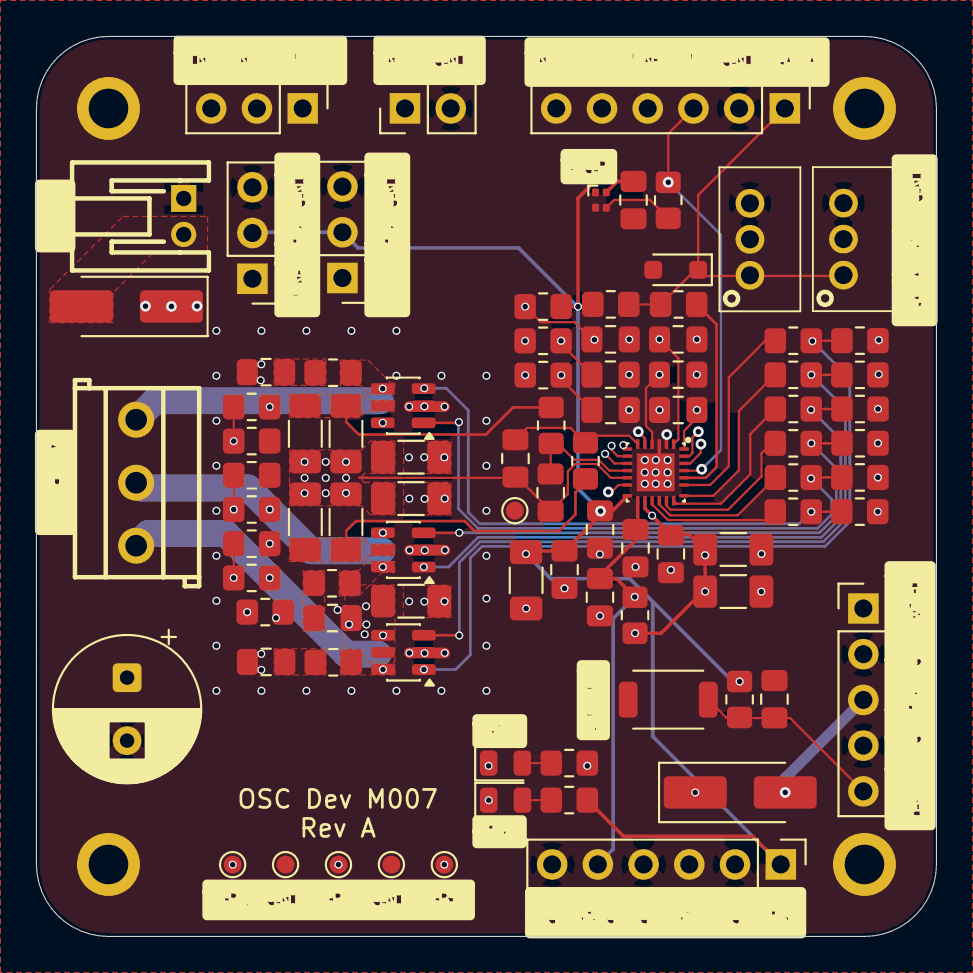
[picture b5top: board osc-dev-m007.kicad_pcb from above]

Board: 6 copper layers, 50.0 x 50.0 mm, 99 parts (0 on the bottom side), 52 nets.

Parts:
C201, C202: 2.2uF; C_0805_2012Metric_Pad1.18x1.45mm_HandSolder
C203, C206, C209, C210, C1002, C1003: 0.1uF; C_0805_2012Metric_Pad1.18x1.45mm_HandSolder
C204, C205, C208, C401, C601, C801: 10uF; C_1206_3216Metric_Pad1.33x1.80mm_HandSolder
C207: 1uF; C_0805_2012Metric_Pad1.18x1.45mm_HandSolder
C301: 470uF 25V; CP_Radial_D8.0mm_P3.50mm
C402, C403, C501, C602, C603, C701, C802, C803, C1001: 1nF; C_0805_2012Metric_Pad1.18x1.45mm_HandSolder
D201: STAT; LED_XL-1010RGBC-WS2812B_1x1mm
D901, D902: SS54; D_SMA_Handsoldering
D1101: PESD5V0L1BA; D_SOD-323_HandSoldering
H101, H102, H103, H104: MountingHole_Pad_MP; MountingHole_2.2mm_M2_ISO7380_Pad
J201: PROG; PinHeader_1x05_P2.54mm_Vertical
J301: BLDC/BDC(A+B); CONN-TH_3P-P3.50_KF350-3.5-3P
J901: JST-PH-H; CONN-TH_S2B-PH-K-S-LF-SN
J1001: NTC_EXT; PinHeader_1x02_P2.54mm_Vertical
J1002: ENC; PinHeader_1x03_P2.54mm_Vertical
J1003: POT; PinHeader_1x03_P2.54mm_Vertical
J1101, J1102: JST-PH-V; CONN-TH_B3B-PH-K-S
J1201, J1202: Conn_01x06; PinHeader_1x06_P2.54mm_Vertical
JP1001: NTC_EXT_INT; PinHeader_1x03_P2.54mm_Vertical
LED901: YELLOW; LED_0805_2012Metric
LED902: GREEN; LED_0805_2012Metric
NT501, NT502, NT701, NT702: NetTie_2; NetTie-2_SMD_0.127mm
Q401, Q601, Q801: SIL3724A-TP; SOT-23-6
R201, R401, R402, R501, R601, R602, R701, R801, R802: 0; R_0805_2012Metric_Pad1.20x1.40mm_HandSolder
R202, R406, R606, R806, R902, R1001, R1102: 10k; R_0805_2012Metric_Pad1.20x1.40mm_HandSolder
R203: 100; R_0805_2012Metric_Pad1.20x1.40mm_HandSolder
R403, R404, R603, R604, R803, R804: 100k; R_0805_2012Metric_Pad1.20x1.40mm_HandSolder
R405, R605, R805: 20k; R_0805_2012Metric_Pad1.20x1.40mm_HandSolder
R407, R607, R807: 10; R_0805_2012Metric_Pad1.20x1.40mm_HandSolder
R901: 22k; R_0805_2012Metric_Pad1.20x1.40mm_HandSolder
R1002, R1003: 4.7k; R_0805_2012Metric_Pad1.20x1.40mm_HandSolder
R1101: 33; R_0805_2012Metric_Pad1.20x1.40mm_HandSolder
R_SH501, R_SH701: 75m; R_1206_3216Metric_Pad1.30x1.75mm_HandSolder
R_SH502, R_SH702: 150m; R_1206_3216Metric_Pad1.30x1.75mm_HandSolder
SW201: RESET; SW_SPST_TS-1088R_3.9x3.0mm
TH1001: 10k 3950K; R_0805_2012Metric_Pad1.20x1.40mm_HandSolder
TP1201, TP1202, TP1203, TP1204, TP1205, TP1206: TestPoint; TestPoint_Pad_D1.0mm
U201: CH32M007E8U7; QFN-26_3x3mm_P0.4mm

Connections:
+5V: C206.1, C207.1, C208.1, C210.1, D201.2 (VDD), J1002.2, J1003.2, J1201.1, R202.1, R902.1, R1001.1, R1102.1, U201.13 (VDD)
/BRIDGE/HALFBRIDGE1/G_H: Q401.3 (G), R401.2, R403.1
/BRIDGE/HALFBRIDGE1/G_L: Q401.1 (G), R402.2, R404.2
/BRIDGE/HALFBRIDGE1/LEG: NT501.1, Q401.5 (S), R_SH501.1, R_SH502.1
/BRIDGE/HALFBRIDGE1/SNUB: C403.1, R407.2
/BRIDGE/HALFBRIDGE2/G_H: Q601.3 (G), R601.2, R603.1
/BRIDGE/HALFBRIDGE2/G_L: Q601.1 (G), R602.2, R604.2
/BRIDGE/HALFBRIDGE2/LEG: NT701.1, Q601.5 (S), R_SH701.1, R_SH702.1
/BRIDGE/HALFBRIDGE2/SNUB: C603.1, R607.2
/BRIDGE/HALFBRIDGE3/G_H: Q801.3 (G), R801.2, R803.1
/BRIDGE/HALFBRIDGE3/G_L: Q801.1 (G), R802.2, R804.2
/BRIDGE/HALFBRIDGE3/SNUB: C803.1, R807.2
/BRIDGE/PH_A: J301.1, Q401.4 (D), Q401.6 (D), R405.1, R407.1
/BRIDGE/PH_B: J301.2, Q601.4 (D), Q601.6 (D), R605.1, R607.1
/BRIDGE/PH_C: J301.3, Q801.4 (D), Q801.6 (D), R805.1, R807.1
/BRIDGE/SHUNT1/ISNS_K: NT501.2, R501.1
/BRIDGE/SHUNT2/ISNS_K: NT701.2, R701.1
/BUS/BUS: R1101.2, U201.22 (TX_5)
/MCU/SWDIO: J201.1, U201.5 (SWIO)
/MCU/nRST: C209.2, J201.5, R202.2, SW201.2, U201.2 (RST)
/POWER/LED_5V: LED902.2 (A), R902.2
/POWER/LED_VSYS: LED901.2 (A), R901.2
/SENSORS/ENC_IN: J1002.1, R1002.2
/SENSORS/NTC_EXT: J1001.1, JP1001.1 (A)
/SENSORS/NTC_INT: JP1001.3 (B), TH1001.1
/SENSORS/POT: J1003.1, R1003.2
DATA: D1101.1 (K), J1101.1, J1102.1, J1202.1, R1101.1, R1102.2
DBG0: TP1201.1 (1_1), U201.25 (PC2)
DBG1: TP1203.1 (1_1), U201.12 (PA5)
DBG2: TP1205.1 (1_1), U201.24 (PC1)
ENC: C1001.2, J1202.4, R1002.1, U201.7 (A7)
GATE_AH: R401.1, U201.16 (HO1)
GATE_AL: R402.1, U201.17 (LO1)
GATE_BH: R601.1, U201.18 (HO2)
GATE_BL: R602.1, U201.19 (LO2)
GATE_CH: R801.1, U201.20 (HO3)
GATE_CL: R802.1, U201.21 (LO3)
GND: C201.2, C202.2, C203.2, C204.2, C205.2, C206.2, C207.2, C208.2, C209.1, C210.2, C301.2, C401.2, C402.2, C403.2, C601.2, C602.2, C603.2, C801.2, C802.2, C803.2, C1001.1, C1002.1, C1003.1, D201.3 (VSS), D1101.2 (A), H101.1 (1_1), H102.1 (1_1), H103.1 (1_1), H104.1 (1_1), J201.2, J201.4, J901.1, J1001.2, J1002.3, J1003.3, J1101.3, J1102.3, J1201.2, J1201.4, J1201.6, J1202.2, LED901.1 (K), LED902.1 (K), NT502.1, NT702.1, Q801.5 (S), R404.1, R406.2, R604.1, R606.2, R804.1, R806.2, R_SH501.2, R_SH502.2, R_SH701.2, R_SH702.2, SW201.1, TH1001.2, TP1202.1 (1_1), TP1204.1 (1_1), TP1206.1 (1_1), U201.3 (VSS)
ISNS1+: C501.1, R501.2, U201.10 (OPP1)
ISNS2+: C701.1, R701.2, U201.6 (OPP2)
ISNS-: C501.2, C701.2, NT502.2, NT702.2, U201.11 (OPN2)
LED: J1202.3, R203.1, U201.23 (T2C3_01)
NTC: C1003.2, J1202.6, JP1001.2 (C), R1001.2, U201.9 (A6)
unnamed: D201.4 (DIN), R203.2
POS: C1002.2, J1202.5, R1003.1, U201.8 (A5)
VBAT: D901.2 (A), J901.2
VHREG: C201.1, C202.1, J1201.5, R201.1, U201.14 (VHREG)
VPROG: D902.2 (A), J201.3
VSNA: C402.1, R405.2, R406.1, U201.1 (A2)
VSNB: C602.1, R605.2, R606.1, U201.4 (A3)
VSNC: C802.1, R805.2, R806.1, U201.26 (A1)
VSYS: C203.1, C204.1, C205.1, C301.1, C401.1, C601.1, C801.1, D901.1 (K), D902.1 (K), J1101.2, J1102.2, J1201.3, Q401.2 (S), Q601.2 (S), Q801.2 (S), R201.2, R403.2, R603.2, R803.2, R901.1, U201.15 (VHV)
